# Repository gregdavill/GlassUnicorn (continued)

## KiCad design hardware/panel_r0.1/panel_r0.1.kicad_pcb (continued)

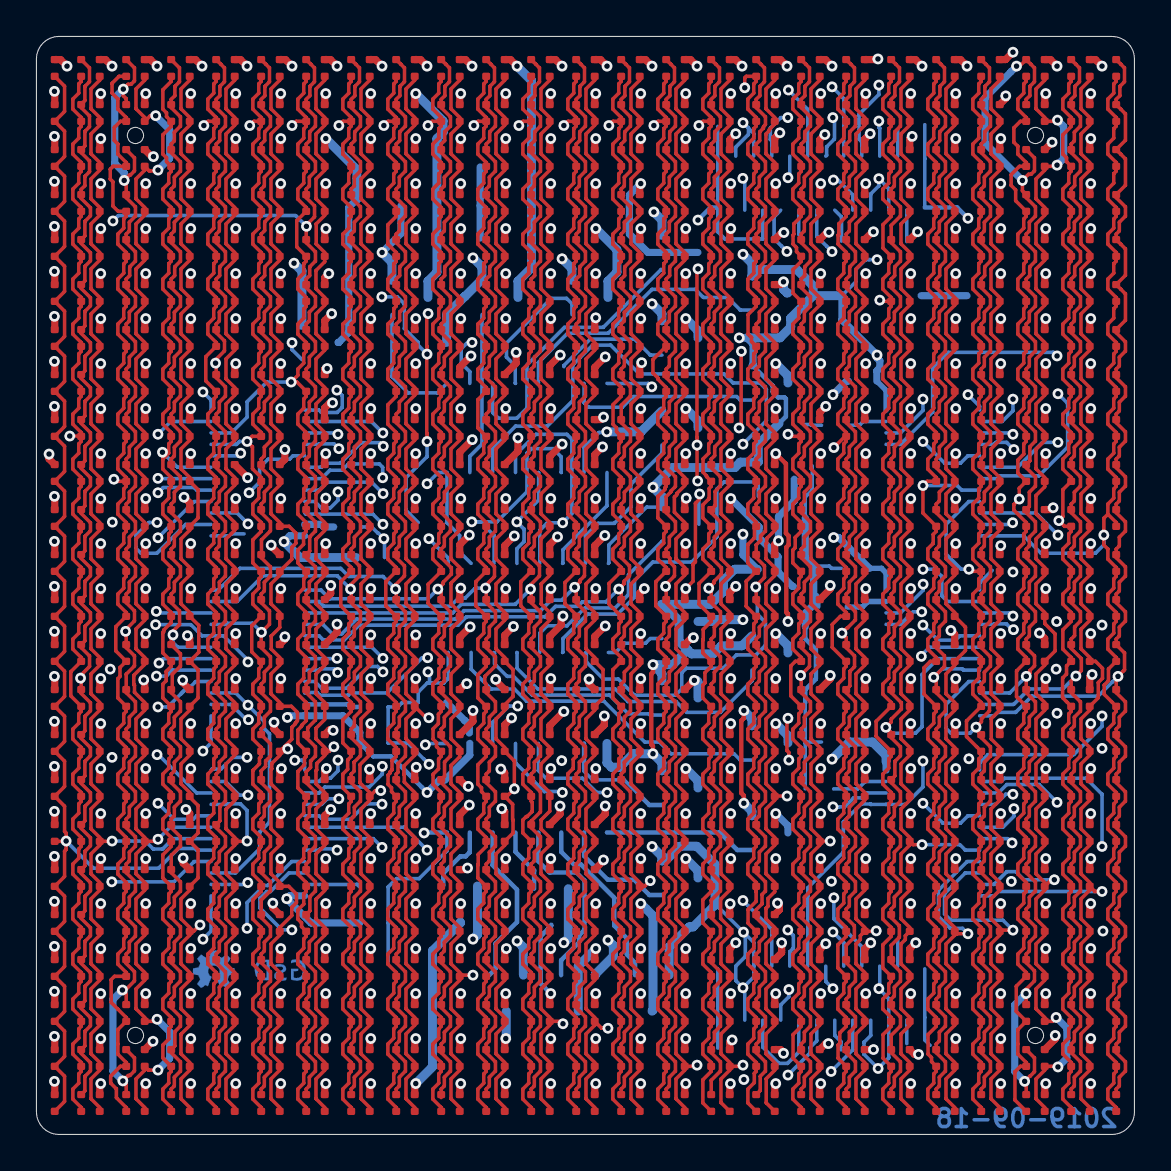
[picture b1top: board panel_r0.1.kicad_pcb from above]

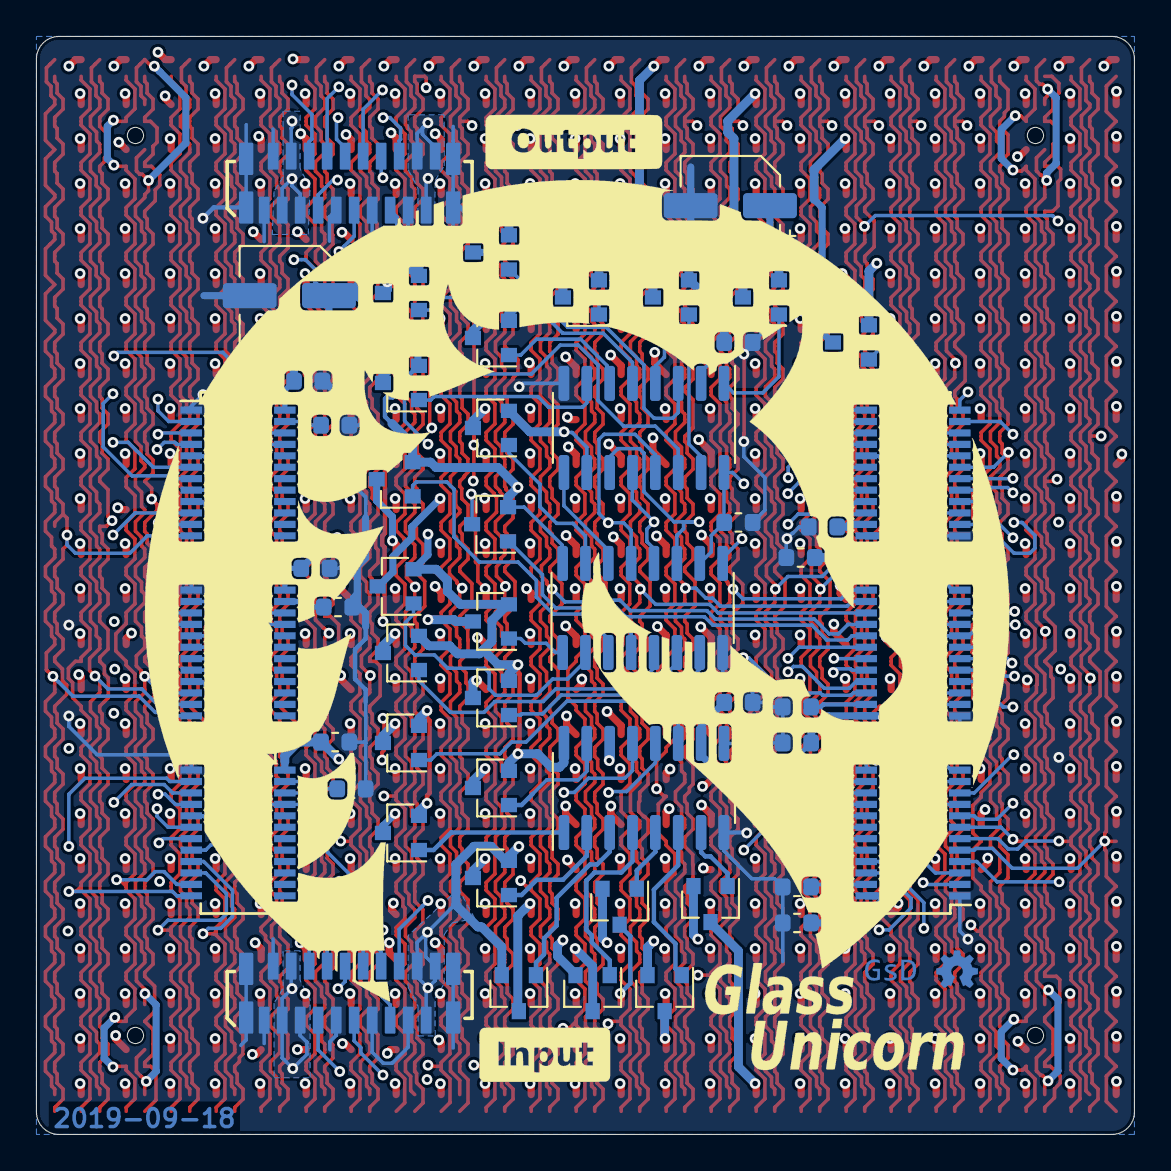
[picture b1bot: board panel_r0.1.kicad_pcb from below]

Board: 4 copper layers, 61.0 x 61.0 mm, 628 parts (52 on the bottom side), 146 nets.

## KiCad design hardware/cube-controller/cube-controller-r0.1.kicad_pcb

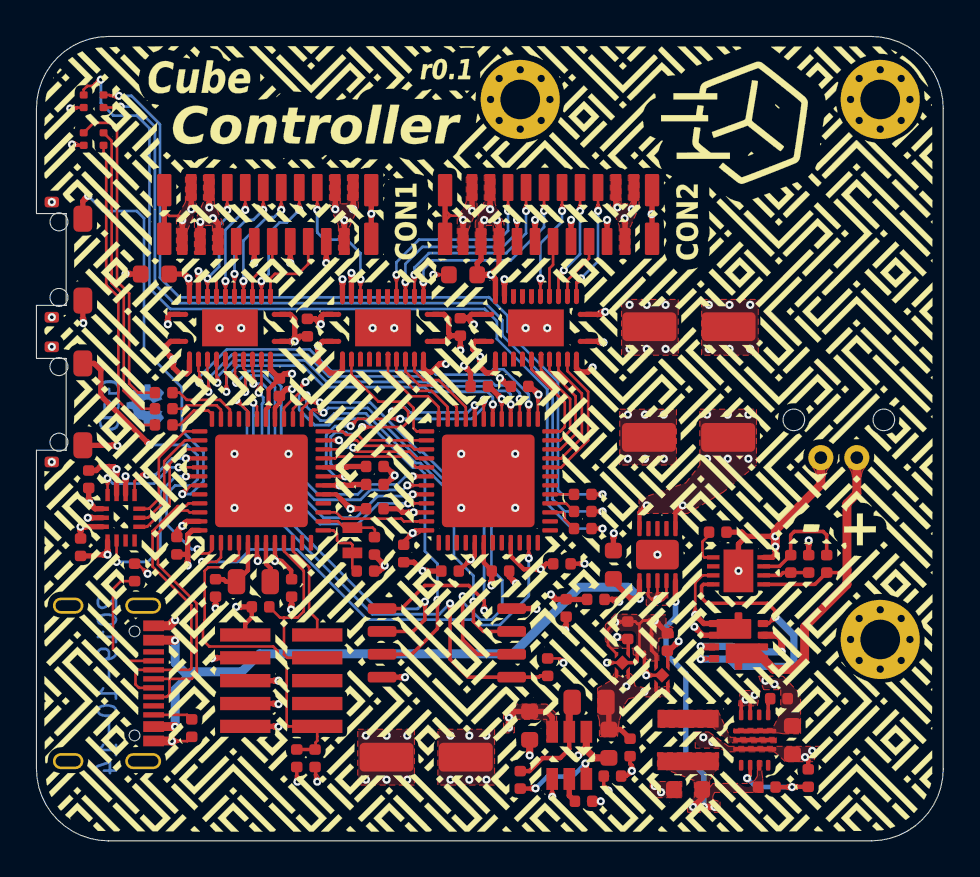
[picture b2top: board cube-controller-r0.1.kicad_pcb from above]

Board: 4 copper layers, 50.4 x 44.7 mm, 83 parts (0 on the bottom side), 103 nets.

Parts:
C1, C2, C4, C5, C26, C28, C33: 10uF; C_0603_1608Metric
C3, C12, C13, C14, C15, C19, C20, C21, C22, C23, C24, C25, C27, C29, C30, C31, C32: 100nF; C_0402_1005Metric
C6, C7, C8, C16: 1uF; C_0402_1005Metric
C9, C10, C11: CP1; CP_Elec_5x3.9
C17, C18: 22pF; C_0402_1005Metric
D1, D2: LED_ARGB; led_rbag_1515
FB1: Ferrite_Bead_Small; L_0402_1005Metric
J1: Conn_01x02; SB02B-PASK-2
J2, J3: Conn_01x20_Shielded; FH12-20S-0.5SVA(54)
J4: Conn_02x05_Odd_Even; FTSH-105-XX-X-DV
J5: USB_C_Receptacle_USB2.0; USB_C_Receptacle_Palconn_UTC16-G
L1: 1uH; L_Coilcraft_XxL4020
L2: 2.2uH; L_0805_2012Metric
L3: 10uH; L_0805_2012Metric
R1: 510k; R_0402_1005Metric
R2, R3: 150k; R_0402_1005Metric
R4: 5.1M; R_0402_1005Metric
R5, R8: 100k; R_0402_1005Metric
R6, R7, R9, R10: R; R_0402_1005Metric
R11, R12, R13, R14, R15, R16: 470R; R_0402_1005Metric
R17, R19, R20: 10k; R_0402_1005Metric
R18: 1k; R_0402_1005Metric
R21, R22: 5.1k; R_0402_1005Metric
SW1, SW2: SW_Push; EVQP4
U1: LTC4367; DFN-8-1EP_3x3mm_P0.5mm_EP1.66x2.38mm
U2: AON7804; DFN3X3_8L_EP2_P
U3: TPS62135; VQFN-11_3x2mm_P0.5mm
U4: TPS561201; TSOT-23-6
U5: NP115-2.5; X2SON_4_1.0x1.0mm
U6: NP115-1.2; X2SON_4_1.0x1.0mm
U7: ATSAMD51G19A; QFN-48-1EP_7x7mm_P0.5mm_EP5.15x5.15mm
U8: ICE40UP5K-SG48ITR; QFN-48-1EP_7x7mm_P0.5mm_EP5.15x5.15mm
U9, U10, U11: SN74AVC8T245PW; Texas_RGY_R-PVQFN-N24_EP2.05x3.1mm
U12: BMX160; Bosch_LGA-14_3x2.5mm_P0.5mm
U13: AT25SF081; SOIC-8_5.23x5.23mm_P1.27mm
U14: LTC4413-2; DFN-10-1EP_3x3mm_P0.5mm_EP1.65x2.38mm
Y1: 32.768kHz; Crystal_SMD_2012-2Pin_2.0x1.2mm

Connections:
1v2: C7.1, C24.1, C25.1, FB1.1, U6.1, U8.5, U8.30
1v2_pll: C8.1, C23.1, FB1.2, U8.29
2v5: C6.1, C22.1, U5.1, U8.24
3v3: C5.1, C12.1, C13.1, C14.1, C15.1, C19.1, C20.1, C21.1, C31.1, C32.1, D1.1, D2.1, J4.1, L2.2, R9.2, R18.2, R19.2, R20.2, U5.3, U5.4, U6.3, U6.4, U7.6, U7.17, U7.36, U7.44, U8.1, U8.22, U8.33, U9.1, U9.2, U10.1, U10.2, U11.1, U11.2, U12.5, U12.8, U13.8
3v3_fb: R9.1, R10.1, U4.4
4v5: C4.1, C9.1, C10.1, C11.1, C26.1, C27.1, C28.1, C29.1, J2.3, J2.4, J2.5, J2.18, J2.19, J2.20, J3.3, J3.4, J3.5, J3.18, J3.19, J3.20, R8.2, U4.3, U9.23, U9.24, U10.23, U10.24, U11.23, U11.24, U14.6, U14.10
4v5_in: C2.1, L1.2, R6.2, U3.6, U14.5
5v0_usb: C33.1, J5.A4, J5.A9, J5.B4, J5.B9, U14.1
5v_fb: R6.1, R7.1, U3.5
unnamed: U2.2, U2.5
unnamed: U1.8, U2.3, U2.6
unnamed: R1.1, U1.5
unnamed: R2.2, R3.1, U1.3
unnamed: R3.2, R4.1, U1.2
unnamed: R5.1, U3.8
unnamed: L1.1, U3.2
unnamed: R8.1, U4.5
unnamed: C3.1, U4.6
unnamed: C3.2, L2.1, U4.2
unnamed: C16.1, L3.2, U7.41
unnamed: R11.1, U7.22
unnamed: R12.1, U7.24
unnamed: R13.1, U7.23
unnamed: C18.1, U7.2, Y1.2
unnamed: C17.1, U7.1, Y1.1
unnamed: R14.1, U8.39
unnamed: R15.1, U8.40
unnamed: R16.1, U8.41
unnamed: U7.38, U8.35
unnamed: U7.3, U8.23
unnamed: SW1.1, U7.37
unnamed: SW2.1, U7.31
unnamed: L3.1, U7.43
cc1: J5.A5, R21.1
cc2: J5.B5, R22.1
gnd: C1.2, C2.2, C4.2, C5.2, C6.2, C7.2, C8.2, C9.2, C10.2, C11.2, C12.2, C13.2, C14.2, C15.2, C16.2, C17.2, C18.2, C19.2, C20.2, C21.2, C22.2, C23.2, C24.2, C25.2, C26.2, C27.2, C28.2, C29.2, C30.2, C31.2, C32.2, C33.2, J1.2, J2.1, J2.2, J2.9, J2.13, J2.17, J2.SH, J3.1, J3.2, J3.9, J3.13, J3.17, J3.SH, J4.3, J4.5, J4.7, J4.9, J5.A1, J5.A12, J5.B1, J5.B12, J5.S1, R1.2, R4.2, R7.2, R10.2, R17.2, R21.2, R22.2, SW1.2, SW2.2, U1.4, U3.3, U3.10, U3.11, U4.1, U5.2, U6.2, U7.5, U7.18, U7.35, U7.42, U7.49, U8.49, U9.11, U9.12, U9.13, U9.22, U10.11, U10.12, U10.13, U10.22, U11.11, U11.12, U11.13, U11.22, U12.2, U12.3, U12.6, U12.7, U13.4, U14.2, U14.3, U14.4, U14.11
ice_config_done: U7.7, U8.7
ice_config_miso: U7.12, U8.14
ice_config_mosi: U7.9, U8.17
ice_config_reset: R17.1, U7.8, U8.8
ice_config_sck: U7.10, U8.15
ice_config_ss: U7.11, U8.16
ice_led_b: D2.4, R16.2
ice_led_g: D2.3, R15.2
ice_led_r: D2.2, R14.2
imu_cs: U7.27, U12.12
imu_int1: U7.29, U12.4
imu_int2: U7.30, U12.9
imu_miso: U7.28, U12.1
imu_mosi: U7.25, U12.14
imu_sck: U7.26, U12.13
led_b: D1.4, R13.2
led_g: D1.3, R12.2
led_r: D1.2, R11.2
pb0_b_blank: J2.12, U9.17
pb0_b_db: J2.8, U9.19
pb0_b_dg: J2.7, U9.20
pb0_b_dr: J2.6, U9.21
pb0_b_latch: J2.11, U9.16
pb0_b_rblank: J2.16, U10.21
pb0_b_rdata: J2.14, U9.15
pb0_b_rlatch: J2.15, U9.14
pb0_b_sclk: J2.10, U9.18
pb0_blank: U8.18, U9.7
pb0_db: U8.4, U9.5
pb0_dg: U8.3, U9.4
pb0_dr: U8.2, U9.3
pb0_latch: U8.19, U9.8
pb0_rblank: U8.13, U10.3
pb0_rdata: U8.20, U9.9
pb0_rlatch: U8.21, U9.10
pb0_sclk: U8.6, U9.6
pb1_b_blank: J3.12, U11.18
pb1_b_db: J3.8, U10.15
pb1_b_dg: J3.7, U10.16
pb1_b_dr: J3.6, U10.17
pb1_b_latch: J3.11, U11.17
pb1_b_rblank: J3.16, U11.14
pb1_b_rdata: J3.14, U11.16
pb1_b_rlatch: J3.15, U11.15
pb1_b_sclk: J3.10, U10.14
pb1_blank: U8.48, U11.6
pb1_db: U8.10, U10.9
pb1_dg: U8.11, U10.8
pb1_dr: U8.12, U10.7
pb1_latch: U8.47, U11.7
pb1_rblank: U8.44, U11.10
pb1_rdata: U8.46, U11.8
pb1_rlatch: U8.45, U11.9
pb1_sclk: U8.9, U10.10
pp_batt: J1.1, R2.1, U1.1, U2.4
pp_batt_prot: C1.1, R5.2, U1.7, U2.1, U3.1
qspi_bus_cs: R20.1, U7.20, U13.1
qspi_bus_io0: U7.13, U13.5
qspi_bus_io1: U7.14, U13.2
qspi_bus_io2: U7.15, U13.3
qspi_bus_io3: U7.16, U13.7
qspi_bus_sck: U7.19, U13.6
samd_rst: C30.1, J4.10, R19.1, U7.40
samd_usb_n: J5.A7, J5.B7, U7.33
samd_usb_p: J5.A6, J5.B6, U7.34
swdclk: J4.4, R18.1, U7.45
swdio: J4.2, U7.46

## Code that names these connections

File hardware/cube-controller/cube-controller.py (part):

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        led_b = Net('led_b')
        led_b += led[4]

        uc['PA13'] += place_part_inline(led_r, res(value='470R',PN='RC0402FR-07470RL', Manf='Yageo'))
        uc['PA15'] += place_part_inline(led_g, res(value='470R',PN='RC0402FR-07470RL', Manf='Yageo'))
        uc['PA14'] += place_part_inline(led_b, res(value='470R',PN='RC0402FR-07470RL', Manf='Yageo'))


        crystal = d_crystal(value='32.768kHz')
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
        swdclk += place_part_inline(pp3v3, res(value='1k',PN='RC0402FR-071KL', Manf='Yageo'))

        uc['PA30', 'PA31'] += swdclk, swdio
        uc['~RESET'] += swdrst        

        uc['~RESET'] += place_part_inline(pp3v3, res(value='10k',PN='RC0402FR-0710KL', Manf='Yageo'))
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        usb_c['GND'] += gnd
        usb_c['SHIELD'] += gnd

        uc['PA24', 'PA25'] += samd_usb_n, samd_usb_p

        # Add Button
        button_a = d_button()
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
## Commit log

2019-09-07 Updated README, added images of project
2019-09-07 Added Panel_r0.1 KiCad files, and scripts
2019-09-07 Added first pass at routing a 32x32 panel.
2019-09-07 Updated 32x32_1515 panel.
2019-09-07 Added README for experimental 32x32 panel design
2019-10-13 Added initial version of Cube controller
2019-10-13 Fix pin1 on SWD connector
2019-10-16 Updated SKiDL to include orderable part numbers. Exported iBOM for r0.1 CubeController Added Gerbers for CubeController r0.1
2019-10-16 Add code to invoke KiCad csv BOM. Generate KiCad csv BOM
2019-10-16 Fix Typo
2021-12-07 Add 3d-printed unibody cube frame
